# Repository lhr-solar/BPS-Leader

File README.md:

# Battery Protection System Leader
All firmware for the Battery Protection System Leader board.

## Setup
Development is done on a Linux environment to build, flash, and debug firmware

Follow this [guide](https://cloud.wikis.utexas.edu/wiki/spaces/LHRSOLAR/pages/28287146/Setting+up+an+Embedded+Development+Environment) to setup an Embedded Development Environment. We primarily use the Windows Subsystem for Linxu (make sure you are using WSL2 and not WSL1).  
After cloning the repo, enter the Embedded-Sharepoint directory an run `./install.sh` to install all needed dependencies. 

### Cloning the Repo
You must clone this repo using SSH. If you do not have an SSH key with Github setup then follow this [guide](https://docs.github.com/en/github/authenticating-to-github/generating-a-new-ssh-key-and-adding-it-to-the-ssh-agent). Note that you must follow the steps while in WSL.

Once SSH is setup and you can this to clone this repository. We append `` --recursive`` to the end to also clone the Embedded-Sharepoint reposistory. 
```
git clone --recursive
```
If you already cloned the repo but don't have the submodules, enter the following commands:

```
git submodule init
git submodule update --remote
```

## Building
Run `make help` for more information on usage.  
When calling any of the following commands, make sure you are in the top level of the repo.

Call `make` to build the release version of the codebase. By default the BPS builds for the STM32F413RHT microcontroller, but you can change that by changing the ` PROJECT_TARGET` field to be the mcu you'd like to compile for

Call `make clean` if the build fails for any reason other than syntax related.

### How to build a test
To build a new test, you need to use the following command:
`make TEST=x` where x is the name of the test file without the .c suffix.

## Flashing
Call `make flash` to flash the most recently built BPS code.  
If using WSL, you must use use usbipd to connect your port to WSL.

There is also a guide on how to flash with the Nucleos [here](https://cloud.wikis.utexas.edu/wiki/spaces/LHRSOLAR/pages/28286498/Flashing+and+debugging+code+on+an+MCU)

## Rules
Commit frequently into your own branches. Create a Pull Request whenever you are ready to add you working code to the master branch. Make sure that your code compiles without any errors or warnings before you open a pull request. At least one approver must approve your pull request before it can be merged. The reviewers will make sure everything is up to par with the coding standards.

### Code Reviews
You can review a pull request even if you are not an approver. In addition to helping us catch bugs, code reviews are a good opportunity to learn more about the BPS codebase. Some examples on what you can include in a code review are:
- Ask why the author wrote a certain part of code in a way they did
- Point out potential bugs in the code
- Point out that part of the code is not well documented or hard to read

You can either approve, comment, or request changes at the end of your pull request. These are the scenarios in which you would use each option:
- **Approve:** You are signing off that this pull request is ready to merge. You and the pull request author "own" this part of the code now.
- **Request Changes:** You have found problems with the code that must be addressed before it can be merged. Note that this will block the pull request from merging until you re-review the code.
- **Comment:** Do this if you do not want to explicitly approve or request changes.

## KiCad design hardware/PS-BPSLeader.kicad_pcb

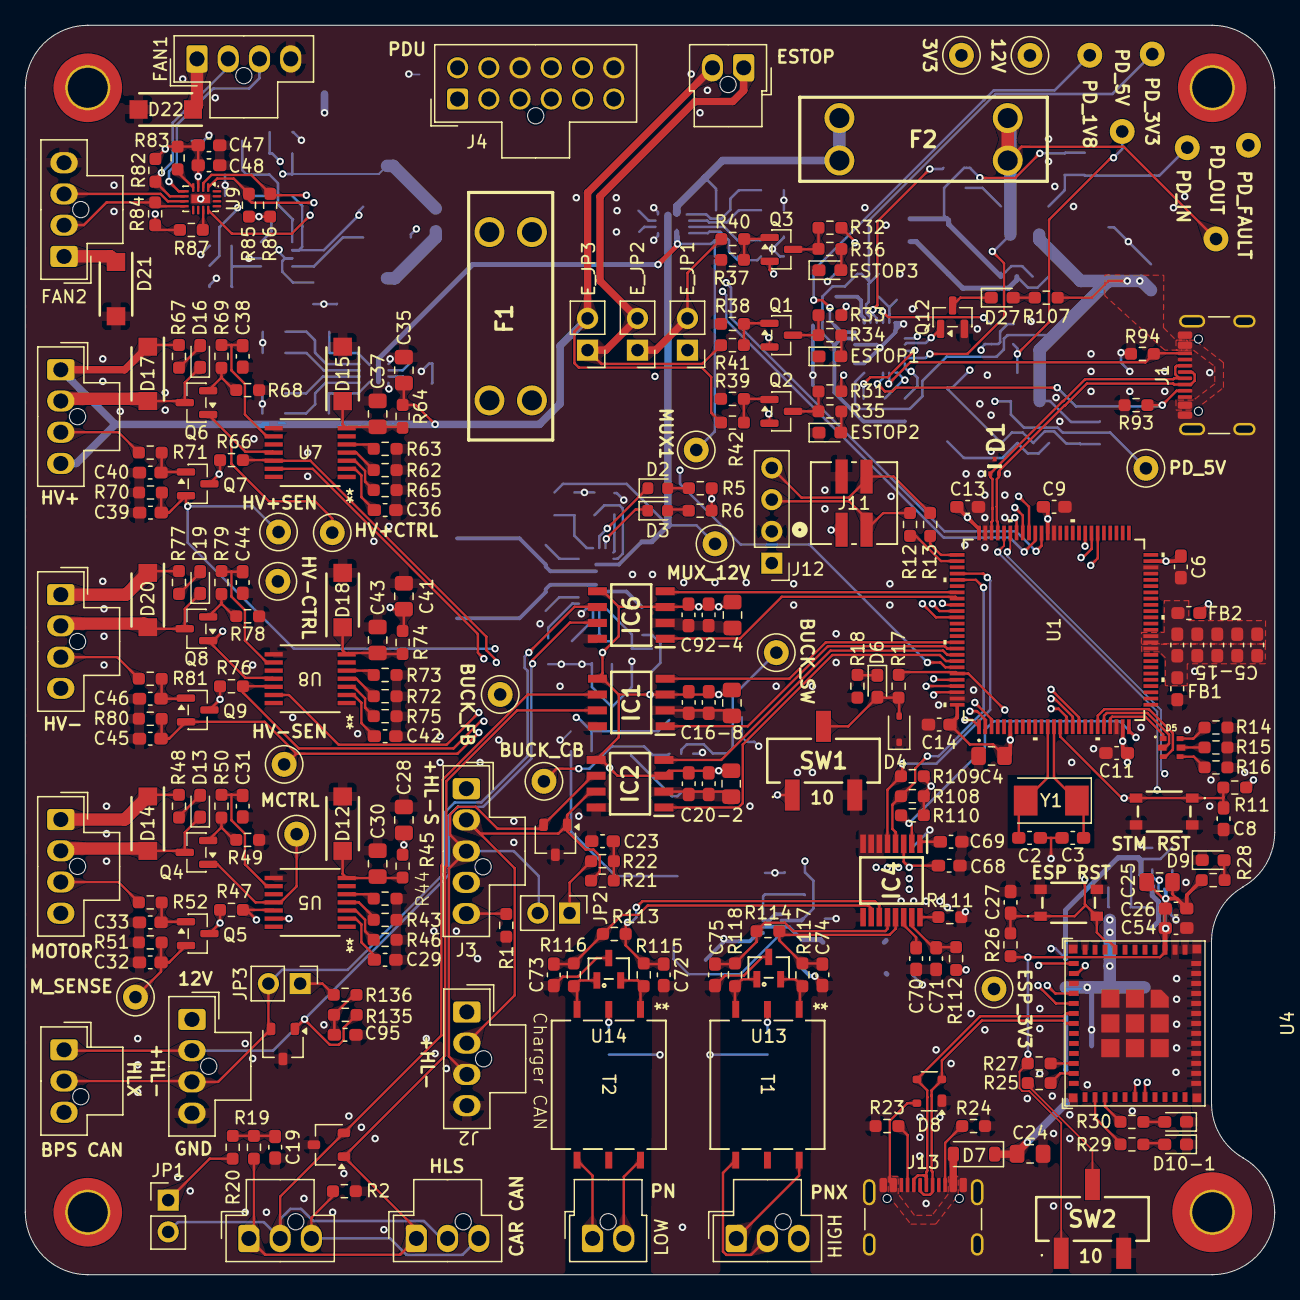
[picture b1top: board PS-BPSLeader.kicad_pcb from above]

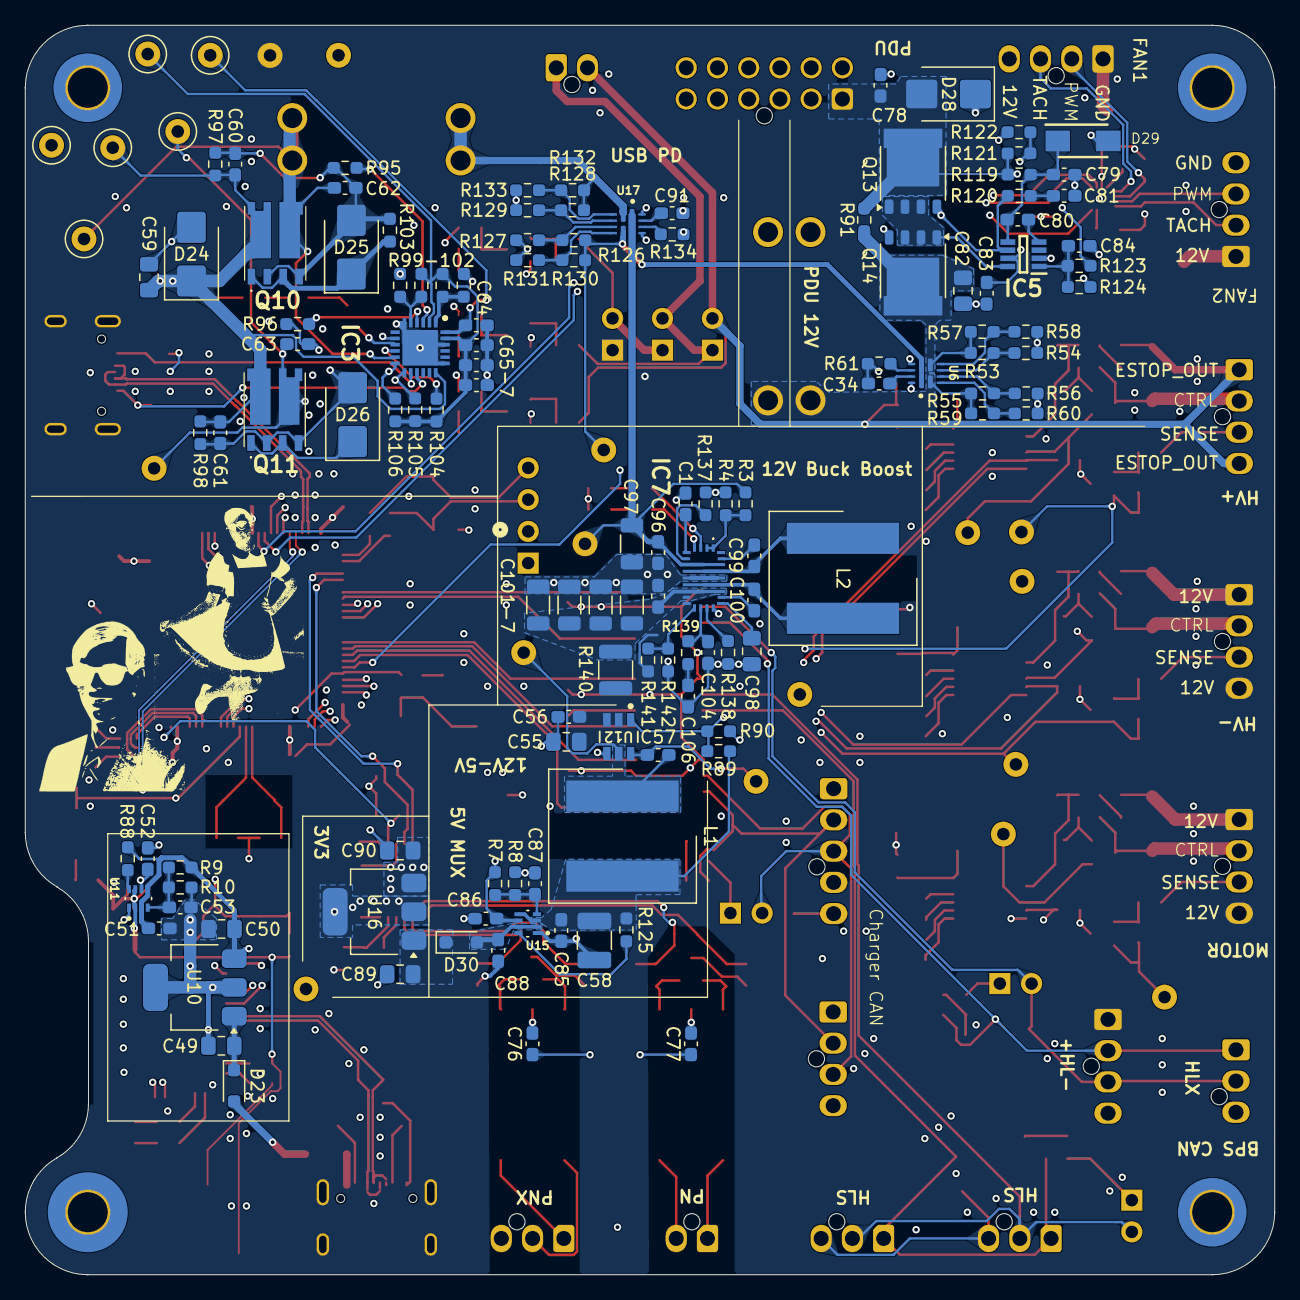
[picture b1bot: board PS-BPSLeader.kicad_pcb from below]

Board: 4 copper layers, 100.0 x 100.0 mm, 385 parts (131 on the bottom side), 230 nets.

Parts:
C1: 7.5n; C_0603_1608Metric_Pad1.08x0.95mm_HandSolder
C2, C3: 26p; C_0603_1608Metric_Pad1.08x0.95mm_HandSolder
C4, C16, C20, C49, C50, C82, C89, C90, C92: 10u; C_0805_2012Metric_Pad1.18x1.45mm_HandSolder
C5, C6, C7, C8, C9, C11, C13, C14, C15, C17, C18, C19, C21, C22, C23, C33, C40, C46, C68, C71, C78, C83, C84, C93, C94, C95, C96, C99, C100, C107: 0.1u; C_0603_1608Metric_Pad1.08x0.95mm_HandSolder
C10, C12, C29, C32, C34, C36, C39, C42, C45, C47, C48, C79, C91: 1u; C_0603_1608Metric_Pad1.08x0.95mm_HandSolder
C24, C25, C59: 10uF; C_0805_2012Metric_Pad1.18x1.45mm_HandSolder
C26, C27, C51, C52, C53, C54, C66, C67, C85, C86, C87, C88: 0.1uF; C_0603_1608Metric_Pad1.08x0.95mm_HandSolder
C28, C30, C35, C37, C41, C43, C55, C98: 4.7u; C_0805_2012Metric_Pad1.18x1.45mm_HandSolder
C31, C38, C44: 0.1n; C_0603_1608Metric_Pad1.08x0.95mm_HandSolder
C56, C57: 100n; C_0603_1608Metric_Pad1.08x0.95mm_HandSolder
C58: 47u; C_1210_3225Metric_Pad1.33x2.70mm_HandSolder
C60, C61, C62, C63, C64, C65: 1uF; C_0603_1608Metric_Pad1.08x0.95mm_HandSolder
C69, C70: 0.22u; C_0603_1608Metric_Pad1.08x0.95mm_HandSolder
C72, C73, C74, C75, C76, C77: 100pF; C_0603_1608Metric_Pad1.08x0.95mm_HandSolder
C80: 220n; C_0603_1608Metric_Pad1.08x0.95mm_HandSolder
C81: 10n; C_0603_1608Metric_Pad1.08x0.95mm_HandSolder
C97, C101, C102, C103, C105: 22u; C_1206_3216Metric
C104: 45p; C_0603_1608Metric_Pad1.08x0.95mm_HandSolder
C106: 90n; C_0603_1608Metric_Pad1.08x0.95mm_HandSolder
D1: TPD2EUSB30DRTR
D2, D3: LED; LED_0603_1608Metric
D4: TVS; D_SOD-323
D5: RGB_LED
D6: LED; LED_0603_1608Metric_Pad1.05x0.95mm_HandSolder
D7: 1N5819HW-7-F; D_SOD-123
D8: SP0503BAHT; SOT-143
D9: ESP_PWR; LED_0603_1608Metric_Pad1.05x0.95mm_HandSolder
D10: ESP_LED1; LED_0603_1608Metric_Pad1.05x0.95mm_HandSolder
D11: ESP_LED2; LED_0603_1608Metric_Pad1.05x0.95mm_HandSolder
D12, D14, D15, D17, D18, D20, D21, D22: VSSAF522-M3/H; SODFL5226X100N
D13, D16, D19: Contact; LED_0603_1608Metric_Pad1.05x0.95mm_HandSolder
D23, D30: SBA130CH-AU_R1_000A1; D_SOD-323_HandSoldering
D24: SMBJ24A-E3_52; D_SMB
D25, D26: SMBJ10A-E3_52; D_SMB
D27: FAULT; LED_0603_1608Metric_Pad1.05x0.95mm_HandSolder
D28: SMBJ15CA; D_SMB
D29: SMAF4758A; SODFL5026X125N
ESTOP1, ESTOP2, ESTOP3: LED; LED_0603_1608Metric_Pad1.05x0.95mm_HandSolder
E_JP1, E_JP2, E_JP3: Jumper_2_Open; PinHeader_1x02_P2.54mm_Vertical
F1, F2: 5A; Fuse-3557-2
FAN1, FAN2: Conn_01x04; Molex_Nano-Fit_105309-xx04_1x04_P2.50mm_Vertical
FB1, FB2: FerriteBead; L_0603_1608Metric_Pad1.05x0.95mm_HandSolder
H1: MountingHole_Pad; MountingHole_3.2mm_M3_Pad_TopBottom
H2, H3, H4: MountingHole_Pad; MountingHole_3.2mm_M3_ISO14580_Pad_TopBottom
IC1, IC2, IC6: TCAN3413DR
IC3: CYPD3177-24LQXQ
IC4: BQ79600PWRQ1; SOP65P640X120-16N
IC5: LM74502DDFR
IC7: TPS552872RYQR; TPS552892QWRYQRQ1
J1, J13: USB_C_Receptacle_USB2.0_16P; USB_C_Receptacle_GCT_USB4105-xx-A_16P_TopMnt_Horizontal
J2: ELCON CAN DEBUG; Molex_Nano-Fit_105309-xx04_1x04_P2.50mm_Vertical
J3: ELCON CAN; Molex_Nano-Fit_105309-xx05_1x05_P2.50mm_Vertical
J4: Conn_02x06_Counter_Clockwise; Molex_Nano-Fit_105310-xx12_2x06_P2.50mm_Vertical
J5: CAR CAN IN; Molex_Nano-Fit_105309-xx03_1x03_P2.50mm_Vertical
J6: CAR CAN OUT; Molex_Nano-Fit_105309-xx03_1x03_P2.50mm_Vertical
J7: BPS CAN DEBUG; Molex_Nano-Fit_105309-xx04_1x04_P2.50mm_Vertical
J8: BPS CAN; Molex_Nano-Fit_105309-xx03_1x03_P2.50mm_Vertical
J9: High Side Conn; Molex_Nano-Fit_105309-xx03_1x03_P2.50mm_Vertical
J10: Low SIde Conn; Molex_Nano-Fit_105309-xx02_1x02_P2.50mm_Vertical
J11: SWD_Header; SWD_Conn
J12: SWD; PinHeader_1x04_P2.54mm_Vertical
J14: Conn_01x02; Molex_Nano-Fit_105309-xx02_1x02_P2.50mm_Vertical
J15, J16, J17: Contactor Connector; Molex_Nano-Fit_105309-xx04_1x04_P2.50mm_Vertical
JP1, JP2, JP3: TRM; PinHeader_1x02_P2.54mm_Vertical
L1: 8.2u; 74439369082
L2: 4.7u; 74439369082
LOGO1: Dr. Hallock; LHRs_LOGO
LOGO2: Dr. Hallock; Hallock_Image_Tiny
Q1, Q2, Q3: SQ2315CES-T1_GE3; SOT-23
Q4, Q5, Q6, Q7, Q8, Q9, Q12: IRLML0030; SOT-23
Q10, Q11: SI7997DP-T1-GE3
Q13, Q14: PSMN012-100YS; LFPAK56
R1, R2, R44, R63, R73, R91: 0; R_0603_1608Metric_Pad0.98x0.95mm_HandSolder
R3: 30.1k; R_0603_1608Metric_Pad0.98x0.95mm_HandSolder
R4, R54, R56, R58, R60, R127, R129, R131, R133: 5k; R_0603_1608Metric_Pad0.98x0.95mm_HandSolder
R5, R6, R14, R15, R16, R18, R28, R29, R30, R34, R35, R36, R45, R50, R64, R69, R74, R79, R95, R96, R101, R113, R114: 1k; R_0603_1608Metric_Pad0.98x0.95mm_HandSolder
R7: 16k; R_0603_1608Metric_Pad0.98x0.95mm_HandSolder
R8, R104: 4.7k; R_0603_1608Metric_Pad0.98x0.95mm_HandSolder
R9: 18k; R_0603_1608Metric_Pad0.98x0.95mm_HandSolder
R10, R11, R17, R25, R26, R27, R31, R32, R33, R37, R38, R39, R47, R51, R52, R66, R70, R71, R76, R80, R81, R82, R84, R85, R86, R88, R97, R107, R108, R109, R119, R125: 10k; R_0603_1608Metric_Pad0.98x0.95mm_HandSolder
R12, R13: 22; R_0603_1608Metric_Pad0.98x0.95mm_HandSolder
R19, R20, R21, R22, R135, R136: 60; R_0603_1608Metric_Pad0.98x0.95mm_HandSolder
R23, R24, R93, R94, R99, R100, R102: 5.1k; R_0603_1608Metric_Pad0.98x0.95mm_HandSolder
R40, R41, R42, R83, R87: 33k; R_0603_1608Metric_Pad0.98x0.95mm_HandSolder
R43, R62, R72: 66.67k; R_0603_1608Metric_Pad0.98x0.95mm_HandSolder
R46, R65, R75: 120k; R_0603_1608Metric_Pad0.98x0.95mm_HandSolder
R48, R67, R77: 4.3k; R_0603_1608Metric_Pad0.98x0.95mm_HandSolder
R49, R68, R78: 1; R_0603_1608Metric_Pad0.98x0.95mm_HandSolder
R53, R126, R132: 57.6k; R_0603_1608Metric_Pad0.98x0.95mm_HandSolder
R55: 67.3k; R_0603_1608Metric_Pad0.98x0.95mm_HandSolder
R57, R130: 26.1k; R_0603_1608Metric_Pad0.98x0.95mm_HandSolder
R59: 37.4k; R_0603_1608Metric_Pad0.98x0.95mm_HandSolder
R61, R134: 22.1k; R_0603_1608Metric_Pad0.98x0.95mm_HandSolder
R89, R110, R111, R121, R123, R128, R141: 100k; R_0603_1608Metric_Pad0.98x0.95mm_HandSolder
R90: 19.1k; R_0603_1608Metric_Pad0.98x0.95mm_HandSolder
R98, R103: 49.9k; R_0603_1608Metric_Pad0.98x0.95mm_HandSolder
R105, R106: 2.2k; R_0603_1608Metric_Pad0.98x0.95mm_HandSolder
R112: 10; R_0603_1608Metric_Pad0.98x0.95mm_HandSolder
R115, R116, R117, R118: 51; R_0603_1608Metric_Pad0.98x0.95mm_HandSolder
R120: 33; R_0603_1608Metric_Pad0.98x0.95mm_HandSolder
R122: 7.32k; R_0603_1608Metric_Pad0.98x0.95mm_HandSolder
R124: 15.8k; R_0603_1608Metric_Pad0.98x0.95mm_HandSolder
R137: 50k; R_0603_1608Metric_Pad0.98x0.95mm_HandSolder
R138: R_US; R_0603_1608Metric_Pad0.98x0.95mm_HandSolder
R139: 1.455k; R_0603_1608Metric_Pad0.98x0.95mm_HandSolder
R140: 12.5m; R_1210_3225Metric
R142: 11.1k; R_0603_1608Metric_Pad0.98x0.95mm_HandSolder
Reset1: Reset; TL3365AF180QG
SW1: SW_SPDT; BootSW
SW2: BOOT Switch; BootSW
SW3: RESET Button; TL3365AF180QG
T1, T2: HMU1228NL; HMU1228NL_PUL
TP1: PD_5V; TestPoint_Loop_D1.80mm_Drill1.0mm_Beaded
TP3: PDU_ELCON; TestPoint_Loop_D1.80mm_Drill1.0mm_Beaded
TP4: MUX_12V; TestPoint_Loop_D1.80mm_Drill1.0mm_Beaded
TP5, TP7, TP9: ctrl; TestPoint_Loop_D1.80mm_Drill1.0mm_Beaded
TP6, TP8, TP10: Sense; TestPoint_Loop_D1.80mm_Drill1.0mm_Beaded
TP11: V_in_12V; TestPoint_Loop_D1.80mm_Drill1.0mm_Beaded
TP12: CB; TestPoint_Loop_D1.80mm_Drill1.0mm_Beaded
TP13: FB; TestPoint_Loop_D1.80mm_Drill1.0mm_Beaded
TP14: SW; TestPoint_Loop_D1.80mm_Drill1.0mm_Beaded
TP15: VBUS_IN; TestPoint_Loop_D1.80mm_Drill1.0mm_Beaded
TP16: PD_VBUS_OUT; TestPoint_Loop_D1.80mm_Drill1.0mm_Beaded
TP17: PD_5V_OUT; TestPoint_Loop_D1.80mm_Drill1.0mm_Beaded
TP18: PD_1V8; TestPoint_Loop_D1.80mm_Drill1.0mm_Beaded
TP19: PD_3V3; TestPoint_Loop_D1.80mm_Drill1.0mm_Beaded
TP20: PD_FAULT; TestPoint_Loop_D1.80mm_Drill1.0mm_Beaded
TP_3.3V1, TP_3.3V2: 3.3V; TestPoint_Loop_D1.80mm_Drill1.0mm_Beaded
U1: STM32G473VETx; 100PinMCU
U2, U3, U18: CDSOT23-T24CAN
U4: ESP32-C6-MINI-1
U5, U7, U8: DRV110APWR; PW14_TEX
U6, U17: TPS2121RUXR
U9: EMC2305-1-AP-TR; QFN-16-1EP_1.8x2.6mm_P0.4mm_EP0.7x1.5mm
U10, U16: MCP1826S; SOT-223-3_TabPin2
U11, U15: TPS2117DRLR
U12: LMR51635XDDCR; DDC0006A-MFG
U13, U14: PESD5V0L2BT; SOT23_NXP
Y1: Crystal; Crystal_SMD_Abracon_ABM3-2Pin_5.0x3.2mm

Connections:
+3.3V: C4.1, C6.1, C9.1, C11.1, C13.1, C14.1, C16.1, C17.1, C18.1, C20.1, C21.1, C22.1, C47.1, C48.1, C52.1, C68.1, C90.2, C92.1, C93.1, C94.1, FB2.1, IC1.3 (VCC), IC1.5 (SHDNV_IO), IC2.3 (VCC), IC2.5 (SHDNV_IO), IC4.3 (VIO), IC6.3 (VCC), IC6.5 (SHDNV_IO), J11.1, J12.1, Q1.2 (S), Q2.2 (S), Q3.2 (S), Q5.3 (D), Q7.3 (D), Q9.3 (D), R5.1, R6.1, R11.2, R47.2, R66.2, R76.2, R82.1, R83.1, R84.1, R85.1, R86.1, R87.1, R108.1, R109.1, R110.1, SW1.1 (A), TP_3.3V2.1 (1_1), U1.6 (VBAT), U1.24 (VDD), U1.49 (VDD), U1.64 (VDD), U1.75 (VDD), U1.100 (VDD), U9.3 (VDD), U11.6 (VIN2), U16.3 (VO)
+3.3V_ESP: C25.1, C25.2, C26.1, C26.2, C54.1, R26.1, R27.2, R28.1, SW2.1 (A), U4.3 (3V3), U11.2 (VOUT), U11.7 (VOUT__1)
+5V: C88.1, D30.2 (A), U15.2 (VOUT), U15.7 (VOUT__1)
+12V: C28.1, C41.1, C55.1, C56.1, D14.1 (K), D20.1 (K), D21.1 (K), D22.1 (K), E_JP1.1 (A), FAN1.1, FAN2.1, IC7.13 (ISN), J7.1 (12V), J15.1 (Con+(12V)), J15.4 (Sense+(12V)), J17.1 (Con+(12V)), J17.4 (Sense+(12V)), R45.2, R48.2, R74.2, R77.2, R112.2, R140.2, R141.2, TP11.1 (1_1), U12.2 (EN), U12.3 (VIN)
/BMS/COMHN: C75.1, IC4.12 (COMHN), R114.2, R118.1
/BMS/COMHP: C74.1, IC4.13 (COMHP), R114.1, R117.1
/BMS/COMLN: C72.1, IC4.11 (COMLN), R113.1, R115.1
/BMS/COMLP: C73.1, IC4.10 (COMLP), R113.2, R116.1
/BMS/INH: IC4.16 (INH), R111.1
/BMS_NFAULT: IC4.2 (NFAULT), R110.2, U1.25 (PA3)
/BMS_UART_RX: IC4.4 (MOSI/RX), R108.2, U1.80 (PC11)
/BMS_UART_TX: IC4.5 (MISO/TX), R109.2, U1.79 (PC10)
/BPS_CAN_H: IC6.7 (CANH), J7.2 (CAN_H), J8.1 (CAN_H), R135.1, U18.1 (CAN_H)
/BPS_CAN_L: IC6.6 (CANL), J7.3 (CAN_L), J8.2 (CAN_L), JP3.2 (B), U18.2 (CAN_L)
/CAR_CAN_H: IC1.7 (CANH), J5.1 (CAN_H), J6.1 (CAN_H), R19.1, U2.1 (CAN_H)
/CAR_CAN_L: IC1.6 (CANL), J5.2 (CAN_L), J6.2 (CAN_L), JP1.2 (B), U2.2 (CAN_L)
/CHARGER_CAN_H: IC2.7 (CANH), J2.2 (CAN_H), J3.2 (CAN_H), R21.1, U3.1 (CAN_H)
/CHARGER_CAN_L: IC2.6 (CANL), J2.3 (CAN_L), J3.3 (CAN_L), JP2.2 (B), U3.2 (CAN_L)
/ELCON_LV+: F1.1, J2.1 (12V), J3.1 (12V)
/ESTOP_1-/2+: E_JP1.2 (B), E_JP2.1 (A), R40.2
/ESTOP_1_SENSE: R32.2, U1.84 (PD2)
/ESTOP_2-: E_JP2.2 (B), E_JP3.1 (A), J14.1, R41.2
/ESTOP_2_SENSE: R33.2, U1.85 (PD3)
/ESTOP_3_SENSE: R31.2, U1.86 (PD4)
/ESTOP_OUT: C35.1, D17.1 (K), E_JP3.2 (B), J14.2, J16.1 (Con+(12V)), J16.4 (Sense+(12V)), R42.2, R64.2, R67.2
/FAN_ALERT: U1.94 (PB7), U9.12 (*ALERT)
/FAN_SCL: R86.2, U1.65 (PC6), U9.2 (SMCLK)
/FAN_SDA: R85.2, U1.66 (PC7), U9.1 (SMDATA)
/Fan/ADDRESS_PULLUP: R83.2, U9.4 (ADDR_SEL)
/Fan/CLK_PULLUP: R87.2, U9.11 (CLK)
/Fan/FAN_1_PWM: FAN1.3, U9.5 (PWM1)
/Fan/FAN_1_TACH: FAN1.2, R82.2, U9.6 (TACH1)
/Fan/FAN_2_PWM: FAN2.3, U9.7 (PWM2)
/Fan/FAN_2_TACH: FAN2.2, R84.2, U9.8 (TACH2)
/HV+ Contactor/Econ_Sense: C38.1, R69.1, U7.9 (SENSE)
/HV+ Contactor/HV_CONTROL: D16.1 (K), D17.2 (A), J16.2 (Con-), Q6.3 (D)
/HV+_CTRL: U1.98 (PE1), U7.13 (EN)
/HV+_ECON: R66.1, U1.97 (PE0), U7.12 (STATUS)
/HV+_SENSE: C39.2, Q7.2 (S), R70.2, TP8.1 (1_1), U1.96 (PB9)
/HV- Contactor/Econ_Sense: C44.1, R79.1, U8.9 (SENSE)
/HV- Contactor/HV_CONTROL: D19.1 (K), D20.2 (A), J17.2 (Con-), Q8.3 (D)
/HV-_CTRL: U1.3 (PE4), U8.13 (EN)
/HV-_ECON: R76.1, U1.2 (PE3), U8.12 (STATUS)
/HV-_SENSE: C45.2, Q9.2 (S), R80.2, TP10.1 (1_1), U1.1 (PE2)
/MOTOR_CTRL: U1.17 (PC2), U5.13 (EN)
/MOTOR_ECON: R47.1, U1.16 (PC1), U5.12 (STATUS)
/MOTOR_SENSE: C32.2, Q5.2 (S), R51.2, TP6.1 (1_1), U1.15 (PC0)
/Motor_Contactor/Econ_Sense: C31.1, R50.1, U5.9 (SENSE)
/Motor_Contactor/HV_CONTROL: D13.1 (K), D14.2 (A), J15.2 (Con-), Q4.3 (D)
/PDU_LV+: C78.1, D28.2 (A2), J4.1, Q13.5, R91.1, R119.2, R121.1, R123.1
/Peripherals/100PinMCU/GNDA: C5.2, C7.2, C10.2, C12.2, C15.2, FB1.1, U1.35 (VSSA)
/Peripherals/100PinMCU/PA0: D5.5, U1.20 (PA0-GPIO_BLUE)
/Peripherals/100PinMCU/PA1: D5.3, U1.21 (PA1-GPIO_RED)
/Peripherals/100PinMCU/PA2: D5.1, U1.22 (PA2-GPIO_GREEN)
/Peripherals/100PinMCU/SWCLK: R12.1, U1.77 (PA14)
/Peripherals/100PinMCU/SWDIO: R13.1, U1.76 (PA13)
/Peripherals/100PinMCU/VDDA: C5.1, C7.1, C10.1, C12.1, C15.1, FB2.2, U1.36 (VREF+), U1.37 (VDDA)
/Peripherals/BPS_CAN_RX: IC6.4 (RXD), U1.82 (PD0)
/Peripherals/BPS_CAN_TX: IC6.1 (TXD), U1.83 (PD1)
/Peripherals/CAR_CAN_RX: IC1.4 (RXD), U1.90 (PB3)
/Peripherals/CAR_CAN_TX: IC1.1 (TXD), U1.91 (PB4)
/Peripherals/CHARGER_CAN_RX: IC2.4 (RXD), U1.92 (PB5)
/Peripherals/CHARGER_CAN_TX: IC2.1 (TXD), U1.93 (PB6)
/Peripherals/ESP32/+5V_LDO_IN: C24.1, D7.1 (K), D23.2 (A)
/Peripherals/ESP32/BOOT: R25.1, U4.23 (GPIO9)
/Peripherals/ESP32/LED1: R29.1, U4.26 (GPIO20)
/Peripherals/ESP32/LED2: R30.1, U4.27 (GPIO21)
/Peripherals/ESP32/USB_D+: D8.2 (K), J13.A6 (D+), J13.B6 (D+), U4.18 (GPIO13/USB_D+)
/Peripherals/ESP32/USB_D-: D8.3 (K), J13.A7 (D-), J13.B7 (D-), U4.17 (GPIO12/USB_D-)
/Peripherals/ESP32/VBUSB: D7.2 (A), D8.4 (K), J13.A4 (VBUS), J13.A9 (VBUS), J13.B4 (VBUS), J13.B9 (VBUS)
/Peripherals/ESP32_LDO/Vout: C50.2, C51.1, R9.1, R88.1, TP_3.3V1.1 (1_1), U10.3 (VO), U11.3 (VIN1), U11.5 (MODE)
/Peripherals/ESP32_Power_Mux/PR1: C53.1, R9.2, R10.1, U11.4 (PR1)
/Peripherals/ESP_GPIO3: U1.56 (PD9), U4.15 (MTCK/GPIO6/ADC1_CH6)
/Peripherals/ESP_GPIO4: U1.57 (PD10), U4.16 (MTDO/GPIO7)
/Peripherals/ESP_NRST: C27.1, R26.2, SW3.1, U1.58 (PD11), U4.8 (EN/CHIP_PU)
/Peripherals/STM_BOOT: R17.1, U1.95 (PB8-BOOT0), U4.12 (GPIO0/ADC1_CH0/XTAL_32K_P)
/Peripherals/STM_NRST: C8.1, R11.1, Reset1.1, U1.14 (PG10-NRST), U4.13 (GPIO1/ADC1_CH1/XTAL_32K_N)
/Peripherals/STM_RX: U1.71 (PA10), U4.31 (U0TXD/GPIO16)
/Peripherals/STM_TX: U1.70 (PA9), U4.30 (U0RXD/GPIO17)
/Power/5V_BUCK: C58.1, C85.1, L1.2, R89.1, R125.1, U15.3 (VIN1), U15.5 (MODE)
/Power/12VBuck/CB: C57.1, TP12.1 (1_1), U12.6 (CB)
/Power/12VBuck/FB: R89.2, R90.1, TP13.1 (1_1), U12.1 (FB)
/Power/12VBuck/SW: C57.2, L1.1, TP14.1 (1_1), U12.5 (SW)
/Power/12V_CC: D3.1 (K), IC7.4 (~CC)
/Power/12V_DITH: C1.1, IC7.5 (DITH/SYNC)
/Power/12V_PG: D2.1 (K), IC7.3 (PG)
/Power/EN: IC7.1 (EN/UVLO), IC7.2 (MODE), R3.2, R4.1
/Power/MUX_12V: C96.1, C97.1, IC7.7 (VIN), R3.1, TP4.1 (1_1), U17.1 (OUT), U17.8 (OUT)
/Power/PDU_12V: C82.1, Q14.5, R53.1, R57.1, R91.2, U6.7 (IN1)
/Power/PD_5V_OUT: C63.1, C86.1, Q11.5 (D2), Q11.6 (D2), Q11.10 (D2), Q11.12 (D2), R7.1, TP1.1 (1_1), TP17.1 (1_1), U15.6 (VIN2)
/Power/PowerProtection/EN/UVLO: C84.2, IC5.1 (EN/UVLO), R123.2, R124.2
/Power/PowerProtection/OV: C83.2, IC5.7 (OV), R121.2, R122.1
/Power/PowerProtection/gate: IC5.6 (GATE), Q13.4, Q14.4, R120.2
/Power/PowerProtection/source: IC5.8 (SRC), Q13.1, Q13.2, Q13.3, Q14.1, Q14.2, Q14.3
/Power/Power_5VMux/PR1: C87.1, R7.2, R8.1, U15.4 (PR1)
/Power/Power_Mux_PD/CP2: R132.2, R133.1, U17.3 (CP2)
/Power/Power_Mux_PD/OV1: R126.2, R127.1, U17.5 (OV1)
/Power/Power_Mux_PD/OV2: R128.2, R129.1, U17.4 (OV2)
/Power/Power_Mux_PD/PRI: R130.2, R131.1, U17.6 (PR1)
/Power/Power_Mux_PD/Vin1: R126.1, R130.1, TP3.1 (1_1), U6.1 (OUT), U6.8 (OUT), U17.7 (IN1)
/Power/Power_Mux_PD/Vin2: F2.2, R128.1, R132.1, U17.2 (IN2)
/Power/Power_Mux_PDU_ELCON/CP2: R59.2, R60.1, U6.3 (CP2)
/Power/Power_Mux_PDU_ELCON/OV1: R53.2, R54.1, U6.5 (OV1)
/Power/Power_Mux_PDU_ELCON/OV2: R55.2, R56.1, U6.4 (OV2)
/Power/Power_Mux_PDU_ELCON/PRI: R57.2, R58.1, U6.6 (PR1)
/Power/Power_Mux_PDU_ELCON/Vin2: F1.2, R55.1, R59.1, U6.2 (IN2)
/Power/Power_USB_PD/ISINK_COARSE: IC3.5 (ISNK_COARSE), R100.2, R102.1
/Power/Power_USB_PD/PD_1V8: C64.2, IC3.24 (VCCD), TP18.1 (1_1)
/Power/Power_USB_PD/PD_3V3: C65.1, C66.1, C67.1, IC3.2 (VBUS_MAX), IC3.23 (VDDD), R99.1, R100.1, R104.1, R105.1, R106.1, TP19.1 (1_1)
/Power/Power_USB_PD/PD_FAULT: IC3.9 (FAULT), Q12.1 (G), TP20.1 (1_1)
/Power/Power_USB_PD/SAFE_PWR_EN: IC3.4 (SAFE_PWR_EN), R96.2
/Power/Power_USB_PD/VBUS_FET_EN: IC3.3 (VBUS_FET_EN), R95.2
/Power/Power_USB_PD/VBUS_MIN: IC3.1 (VBUS_MIN), R99.2, R101.1
/Power/USB_PD_OUT: C62.1, F2.1, IC3.11 (VDC_OUT), Q10.5 (D2), Q10.6 (D2), Q10.10 (D2), Q10.12 (D2), TP16.1 (1_1)
/SHIELD: J5.3 (SHIELD), J6.3 (SHIELD), R2.1
/USB_CC1: IC3.15 (CC1), J1.A5 (CC1), R93.1
/USB_CC2: IC3.14 (CC2), J1.B5 (CC2), R94.1
/USB_D+: D1.1 (D+), J1.A6 (D+), J1.B6 (D+), U1.73 (PA12)
/USB_D-: D1.2 (D-), J1.A7 (D-), J1.B7 (D-), U1.72 (PA11)
/USB_GPIO: IC3.8 (GPIO_1), U1.69 (PA8)
/USB_SCL: IC3.13 (HPI_SCL), R105.2, U1.67 (PC8)
/USB_SDA: IC3.12 (HPI_SDA), R106.2, U1.68 (PC9)
/USB_VBUS_IN: C59.1, C60.1, C61.1, D24.1 (K), IC3.18 (VBUS_IN), J1.A4 (VBUS), J1.A9 (VBUS), J1.B4 (VBUS), J1.B9 (VBUS), Q10.7 (D1), Q10.8 (D1), Q10.9 (D1), Q10.11 (D1), Q11.7 (D1), Q11.8 (D1), Q11.9 (D1), Q11.11 (D1), R97.2, R98.2, R107.1, TP15.1 (1_1)
/isolatedCOMHN: J9.2, T1.4 (TX-)
/isolatedCOMHP: J9.1, T1.6 (TX+)
/isolatedCOMLN: J10.2, T2.6 (TX+)
/isolatedCOMLP: J10.1, T2.4 (TX-)
GND: C1.2, C2.1, C3.1, C4.2, C6.2, C8.2, C9.2, C11.2, C13.2, C14.2, C16.2, C17.2, C18.2, C19.2, C20.2, C21.2, C22.2, C23.2, C24.2, C27.2, C28.2, C29.2, C30.2, C31.2, C32.1, C33.1, C34.2, C35.2, C36.2, C37.2, C38.2, C39.1, C40.1, C41.2, C42.2, C43.2, C44.2, C45.1, C46.1, C47.2, C48.2, C49.1, C50.1, C51.2, C52.2, C53.2, C54.2, C55.2, C56.2, C58.2, C59.2, C64.1, C65.2, C66.2, C67.2, C68.2, C69.2, C70.2, C71.2, C72.2, C73.2, C74.2, C75.2, C76.1, C77.1, C78.2, C79.1, C81.2, C82.2, C83.1, C84.1, C85.2, C86.2, C87.2, C88.2, C89.1, C90.1, C91.2, C92.2, C93.2, C94.2, C95.2, C96.2, C97.2, C98.2, C101.2, C102.2, C103.2, C104.2, C105.2, C106.2, C107.2, D1.3 (GND), D4.1 (A1), D8.1 (A), D9.1 (K), D10.1 (K), D11.1 (K), D12.2 (A), D15.2 (A), D18.2 (A), D21.2 (A), D22.2 (A), D24.2 (A), D28.1 (A1), D29.2 (A), ESTOP1.1 (K), ESTOP2.1 (K), ESTOP3.1 (K), FAN1.4, FAN2.4, FB1.2, IC1.2 (GND), IC1.8 (STB), IC2.2 (GND), IC2.8 (STB), IC3.6 (ISNK_FINE), IC3.19 (GND_1), IC3.22 (GND_2), IC3.25 (GND_3), IC4.6 (SCLK), IC4.7 (NCS), IC4.8 (NUART/SPI_(SPI_RDY)), IC4.9 (GND), IC5.2 (GND), IC6.2 (GND), IC6.8 (STB), IC7.9 (PGND_1), IC7.17 (AGND), IC7.22 (PGND_2), IC7.23 (PGND_3), J1.A1 (GND), J1.A12 (GND), J1.B1 (GND), J1.B12 (GND), J1.S1 (SHIELD), J1.S2 (Shield), J1.S3 (Shield), J1.S4 (Shield), J2.4 (GND), J3.4 (GND), J4.9, J4.12, J7.4 (GND), J11.2, J12.2, J13.A1 (GND), J13.A12 (GND), J13.B1 (GND), J13.B12 (GND), J13.S1 (SHIELD), J13.S2 (Shield), J13.S3 (Shield), J13.S4 (Shield), Q12.2 (S), R1.2, R2.2, R4.2, R8.2, R10.2, R14.2, R15.2, R16.2, R18.2, R23.2, R24.2, R37.1, R38.1, R39.1, R43.1, R44.1, R46.1, R49.1, R51.1, R54.2, R56.2, R58.2, R60.2, R61.2, R62.1, R63.1, R65.1, R68.1, R70.1, R72.1, R73.1, R75.1, R78.1, R80.1, R90.2, R93.2, R94.2, R101.2, R102.2, R111.2, R122.2, R124.1, R127.2, R129.2, R131.2, R133.2, R134.2, R137.1, R138.1, R142.2, Reset1.2, SW1.3 (C), SW2.3 (C), SW3.2, U1.23 (VSS), U1.48 (VSS), U1.63 (VSS), U1.74 (VSS), U1.99 (VSS), U2.3 (GND), U3.3 (GND), U4.1 (GND), U4.2 (GND), U4.11 (GND), U4.14 (GND), U4.36 (GND), U4.37 (GND), U4.38 (GND), U4.39 (GND), U4.40 (GND), U4.41 (GND), U4.42 (GND), U4.43 (GND), U4.44 (GND), U4.45 (GND), U4.46 (GND), U4.47 (GND), U4.48 (GND), U4.49 (GND), U4.50 (GND), U4.51 (GND), U4.52 (GND), U4.53 (GND), U5.8 (GND), U6.9 (ST), U6.12 (GND), U7.8 (GND), U8.8 (GND), U9.17 (EPAD), U10.2 (GND), U11.1 (GND), U12.4 (GND), U13.3, U14.3, U15.1 (GND), U16.2 (GND), U17.9 (ST), U17.12 (GND), U18.3 (GND)
unnamed: C19.1, R19.2, R20.1
unnamed: C23.1, R21.2, R22.1
unnamed: C81.1, R120.1
unnamed: C95.1, R135.2, R136.1
unnamed: C106.1, R139.2
unnamed: D2.2 (A), R5.2
unnamed: D3.2 (A), R6.2
unnamed: D4.2 (A2), D6.2 (A), R17.2, SW1.2 (B)
unnamed: D5.2, R14.1
unnamed: D5.4, R15.1
unnamed: D5.6, R16.1
unnamed: D6.1 (K), R18.1
unnamed: D9.2 (A), R28.2
unnamed: D10.2 (A), R29.2
unnamed: D11.2 (A), R30.2
unnamed: C30.1, D12.1 (K), R45.1, U5.7 (VIN)
unnamed: D13.2 (A), R48.1
unnamed: C37.1, D15.1 (K), R64.1, U7.7 (VIN)
unnamed: D16.2 (A), R67.1
unnamed: C43.1, D18.1 (K), R74.1, U8.7 (VIN)
unnamed: D19.2 (A), R77.1
unnamed: C49.2, D23.1 (K), U10.1 (VI)
unnamed: C60.2, C62.2, D25.2 (A), Q10.2 (G1), Q10.4 (G2), R95.1, R97.1, R103.1
unnamed: D25.1 (K), Q10.1 (S1), Q10.3 (S2), R103.2
unnamed: C61.2, C63.2, D26.2 (A), Q11.2 (G1), Q11.4 (G2), R96.1, R98.1
unnamed: D26.1 (K), Q11.1 (S1), Q11.3 (S2)
unnamed: D27.2 (A), R107.2
unnamed: D27.1 (K), Q12.3 (D)
unnamed: C79.2, C80.1, D29.1 (K), IC5.5 (VS), R119.1
unnamed: C89.2, D30.1 (K), U16.1 (VI)
unnamed: ESTOP1.2 (A), R34.2
unnamed: ESTOP2.2 (A), R35.2
unnamed: ESTOP3.2 (A), R36.2
unnamed: IC3.10 (FLIP), R104.2
unnamed: C71.1, IC4.15 (BAT), R112.1
unnamed: C70.1, IC4.14 (CVDD)
unnamed: C69.1, IC4.1 (DVDD)
unnamed: C80.2, IC5.4 (VCAP)
unnamed: C99.1, IC7.20 (BOOT1)
unnamed: C100.2, IC7.19 (BOOT2)
unnamed: IC7.16 (CDC), R138.2
unnamed: C104.1, IC7.15 (COMP), R139.1
unnamed: IC7.14 (FB), R141.1, R142.1
unnamed: IC7.6 (FSW), R137.2
unnamed: C101.1, C102.1, C103.1, C105.1, C107.1, IC7.11 (VOUT), IC7.12 (ISP), R140.1
unnamed: C99.2, IC7.8 (SW1), L2.1
unnamed: C100.1, IC7.10 (SW2), L2.2
unnamed: C98.1, IC7.18 (VCC)
unnamed: J3.5 (SHIELD), R1.1
unnamed: J11.3, J12.3, R12.2
unnamed: J11.4, J12.4, R13.2
unnamed: J13.A5 (CC1), R23.1
unnamed: J13.B5 (CC2), R24.1
unnamed: J15.3 (Sense-), R52.1
unnamed: J16.3 (Sense-), R71.1
unnamed: J17.3 (Sense-), R81.1
unnamed: JP1.1 (A), R20.2
unnamed: JP2.1 (A), R22.2
unnamed: JP3.1 (A), R136.2
unnamed: Q1.3 (D), R33.1, R34.1
unnamed: Q1.1 (G), R38.2, R41.1
unnamed: Q2.3 (D), R31.1, R35.1
unnamed: Q2.1 (G), R39.2, R42.1
unnamed: Q3.3 (D), R32.1, R36.1
unnamed: Q3.1 (G), R37.2, R40.1
unnamed: Q4.1 (G), TP5.1 (1_1), U5.11 (OUT)
unnamed: Q4.2 (S), R49.2, R50.2
unnamed: C33.2, Q5.1 (G), R52.2
unnamed: Q6.1 (G), TP7.1 (1_1), U7.11 (OUT)
unnamed: Q6.2 (S), R68.2, R69.2
unnamed: C40.2, Q7.1 (G), R71.2
unnamed: Q8.1 (G), TP9.1 (1_1), U8.11 (OUT)
unnamed: Q8.2 (S), R78.2, R79.2
unnamed: C46.2, Q9.1 (G), R81.2
unnamed: R25.2, SW2.2 (B)
unnamed: C76.2, T1.2 (TCT)
unnamed: R117.2, T1.1 (TD+), U13.2
unnamed: R118.2, T1.3 (TD-), U13.1
unnamed: C77.2, T2.2 (TCT)
unnamed: R115.2, T2.1 (TD+), U14.2
unnamed: R116.2, T2.3 (TD-), U14.1
unnamed: C2.2, U1.12 (PF0-OSC_IN), Y1.2
unnamed: C3.2, U1.13 (PF1-OSC_OUT), Y1.1
unnamed: R27.1, U4.22 (GPIO8)
unnamed: R43.2, U5.4 (HOLD)
unnamed: C29.1, U5.2 (KEEP)
unnamed: R44.2, U5.5 (OSC)
unnamed: R46.2, U5.3 (PEAK)
unnamed: R61.1, U6.10 (ILIM)
unnamed: C34.1, U6.11 (SS)
unnamed: R62.2, U7.4 (HOLD)
unnamed: C36.1, U7.2 (KEEP)
unnamed: R63.2, U7.5 (OSC)
unnamed: R65.2, U7.3 (PEAK)
unnamed: R72.2, U8.4 (HOLD)
unnamed: C42.1, U8.2 (KEEP)
unnamed: R73.2, U8.5 (OSC)
unnamed: R75.2, U8.3 (PEAK)
unnamed: R88.2, U11.8 (ST)
unnamed: R125.2, U15.8 (ST)
unnamed: R134.1, U17.10 (ILIM)
unnamed: C91.1, U17.11 (SS)

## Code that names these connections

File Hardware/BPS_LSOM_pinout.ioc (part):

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Mcu.Name=STM32G473R(B-C-E)Tx
Mcu.Package=LQFP64
Mcu.UserName=STM32G473RETx
PA0.Signal=GPIO_Output
PA1.Signal=GPIO_Output
PA10.Signal=GPIO_Input
PA11.Mode=FDCAN_Activate
PA11.Signal=FDCAN1_RX
PA12.Mode=FDCAN_Activate
PA12.Signal=FDCAN1_TX
PA13.Mode=Serial_Wire
PA13.Signal=SYS_JTMS-SWDIO
PA14.Mode=Serial_Wire
PA14.Signal=SYS_JTCK-SWCLK
PA15.Mode=FDCAN_Activate
PA15.Signal=FDCAN3_TX
PA2.Signal=GPIO_Input
PA3.Signal=GPIO_Input
PA4.Mode=NSS_Signal_Hard_Output
PA4.Signal=SPI1_NSS
PA5.Mode=Full_Duplex_Master
PA5.Signal=SPI1_SCK
PA6.Mode=Full_Duplex_Master
PA6.Signal=SPI1_MISO
PA7.Mode=Full_Duplex_Master
PA7.Signal=SPI1_MOSI
PA8.Mode=FDCAN_Activate
PA8.Signal=FDCAN3_RX
PA9.Mode=IN2-Single-Ended
PA9.Signal=ADC5_IN2
PB0.Signal=GPIO_Input
PB10.Mode=Asynchronous
PB10.Signal=USART3_TX
PB11.Mode=Asynchronous
PB11.Signal=USART3_RX
PB12.Mode=IN11-Single-Ended
PB12.Signal=ADC1_IN11
PB2.Mode=IN12-Single-Ended
PB2.Signal=ADC2_IN12
PB3.Signal=GPIO_Input
PB4.Signal=GPIO_Input
PB5.Signal=GPIO_Input
PB6.Signal=GPIO_Output
PB7.Signal=GPIO_Input
PB8-BOOT0.Signal=GPIO_Input
PC0.Signal=GPIO_Input
PC1.Signal=GPIO_Output
PC10.Mode=Asynchronous
PC10.Signal=UART4_TX
PC11.Mode=Asynchronous
PC11.Signal=UART4_RX
PC12.Signal=GPIO_Output
PC2.Signal=GPIO_Output
PC3.Mode=IN9-Single-Ended
PC3.Signal=ADC1_IN9
PC6.Mode=I2C
PC6.Signal=I2C4_SCL
PC7.Mode=I2C
PC7.Signal=I2C4_SDA
PC8.Mode=I2C
PC8.Signal=I2C3_SCL
PC9.Mode=I2C
PC9.Signal=I2C3_SDA
PD2.Signal=GPIO_Output
PF0-OSC_IN.Mode=HSE-External-Oscillator
PF0-OSC_IN.Signal=RCC_OSC_IN
PF1-OSC_OUT.Mode=HSE-External-Oscillator
PF1-OSC_OUT.Signal=RCC_OSC_OUT
PG10-NRST.Signal=GPIO_Input
RCC.HSE_VALUE=8000000
RCC.SYSCLKFreq_VALUE=16000000
board=custom

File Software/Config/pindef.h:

/* File holds all pin, port, and channel definitions*/

/**
 * @brief object that holds pin num and port of a GPIO pin
 */
typedef struct {
    GPIO_TypeDef* port; // e.g., GPIOA
    uint16_t      pin;  // e.g., GPIO_PIN_3
} GpioPin_t;



// Strobe Connection (+3.3V)
#define STROBE_PIN  GPIO_PIN_2
#define STROBE_PORT GPIOD


// Indication Connection 
#define INDICATION_PIN  GPIO_PIN_12
#define INDICATION_PORT GPIOC

// Heartbeat LED
#define HEARTBEAT_LED_PIN  GPIO_PIN_3
#define HEARTBEAT_LED_PORT GPIOC


// Fan Cip
//------------------------------------------
#define FAN_SCL_PIN GPIO_PIN_8 
#define FAN_SCL_PORT GPIOC

#define FAN_SDA_PIN GPIO_PIN_9
#define FAN_SDA_PORT GPIOC

#define FAN_ALERT_PIN GPIO_PIN_0
#define FAN_ALERT_PORT GPIOC

#define FAN_I2C_CHANNEL I2C3
//------------------------------------------


// SHT4x
//------------------------------------------
#define SHT4x_SCL_PIN GPIO_PIN_6 
#define SHT4x_SCL_PORT GPIOC

#define SHT4x_SDA_PIN GPIO_PIN_7
#define SHT4x_SDA_PORT GPIOC

#define SHT4x_I2C_CHANNEL I2C4
//------------------------------------------


// ESP32
//------------------------------------------
#define ESP_RESET_PIN GPIO_PIN_1 
#define ESP_RESET_PORT GPIOB

#define ESP_UART_CHANNEL LPUART1
//------------------------------------------


// Status LED Shift-Reg PINDEF
//------------------------------------------
#define LED_SER_PIN GPIO_PIN_13  
#define LED_SER_PORT GPIOB

#define LED_RCLK_PIN GPIO_PIN_15 
#define LED_RCLK_PORT GPIOB

#define LED_SRCLK_PIN GPIO_PIN_14
#define LED_SRCLK_PORT GPIOB
//------------------------------------------


// ADC Precharge V
//------------------------------------------
#define ARRAY_V_PIN ADC_NUM_11
#define ARRAY_V_CHANNEL ADC1


#define BATT_V_PIN ADC_NUM_12
#define BATT_V_PORT ADC2
//------------------------------------------


// Car and BPS CAN 
//------------------------------------------
#define BPS_CAN_CHANNEL FDCAN1

#define CAR_CAN_CHANNEL FDCAN3
//------------------------------------------


// HV+ Contactor
//------------------------------------------
#define HV_PLUS_CONTROL_PIN GPIO_PIN_2
#define HV_PLUS_CONTROL_PORT GPIOC

#define HV_PLUS_SENSE_PIN GPIO_PIN_2
#define HV_PLUS_SENSE_PORT GPIOA
//------------------------------------------


// HV- Contactor
//------------------------------------------
#define HV_MINUS_CONTROL_PIN GPIO_PIN_0
#define HV_MINUS_CONTROL_PORT GPIOB

#define HV_MINUS_SENSE_PIN GPIO_PIN_1
#define HV_MINUS_SENSE_PORT GPIOA
//------------------------------------------


// Array Contactor
//------------------------------------------
#define ARRAY_CONTROL_PIN GPIO_PIN_1
#define ARRAY_CONTROL_PORT GPIOC

#define ARRAY_SENSE_PIN GPIO_PIN_0
#define ARRAY_SENSE_PORT GPIOA
//------------------------------------------


// Array Precharge Contactor
//------------------------------------------
#define ARRAY_PRE_CONTROL_PIN GPIO_PIN_9
#define ARRAY_PRE_CONTROL_PORT GPIOB            

#define ARRAY_PRE_SENSE_PIN GPIO_PIN_3
#define ARRAY_PRE_SENSE_PORT GPIOB
//------------------------------------------


// ESTOPs
//------------------------------------------
#define ESTOP1_PIN GPIO_PIN_5
#define ESTOP1_PORT GPIOB

#define ESTOP2_PIN GPIO_PIN_10
#define ESTOP2_PORT GPIOA

#define ESTOP3_PIN GPIO_PIN_4
#define ESTOP3_PORT GPIOB
//------------------------------------------

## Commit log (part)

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2024-04-13 fixed gitignore
2024-04-16 still no compile :(
2024-04-17 added a main (still no compile)
2024-04-17 leader compiles
2024-10-05 initial commit: empty makefile
2024-10-12 embedded-sharepoint compiles with make
2024-10-12 actually compiles embedded sharepoint now
2024-10-12 improved makefile
2024-10-12 better clean
2024-10-19 builds? production code
2024-10-26 builds with test file, error with main
2024-10-26 builds both main & test (but it's hardcoded)
2024-10-26 everything seems to compile properly (compiling for test now excludes main.c)
2024-10-26 improved "make help"; everything compiles
2024-10-26 test folder
2024-10-26 initial makefile review (#1)
    * initial commit: empty makefile
    * embedded-sharepoint compiles with make
    * actually compiles embedded sharepoint now
    * improved makefile
    * added clean in Makefile
    * better clean
2024-11-02 first IDWG draft
2024-11-02 modified makefile to allow passed-in stm targets
2024-11-06 started adding structure
2024-11-06 started messing with Readme
2024-11-06 wahooo
2024-11-06 addded config
2024-11-09 restructure
2024-11-09 fixed flash for my makefile
2024-11-09 fixed ghot spaces in default project target
2024-11-10 still messing with stuff
2024-11-10 dumbass
2024-11-10 fixed some stuff
2024-11-10 who needs to test code
2024-11-13 started testing tasks
2024-11-13 the OS is not OSing
2024-11-15 init task doesn't brick itself
2024-11-16 confirmed flash to nucleo, IWDG continuosly resets though
2024-11-16 IWDG refreshes in time, but with funky timeout
2024-11-16 documented some issues
2024-11-16 IWDG seems to work
2024-12-07 end of workday 12/7/24
2024-12-07 changed c_cpp properties
2024-12-14 20ms timeout, but HAL_Delay(17) trips IWDG
2025-01-11 Updated makefile
2025-01-11 upated safe directory
2025-01-11 pls wokr :sob:
2025-01-11 removed lame comment
2025-01-11 update Embedded-Sharepoint
2025-01-12 removed not needed git safes in devcontainer
2025-01-12 ok maybe i did need it
2025-01-12 let's see if i rlly need it
2025-01-12 lmao i forgot bear
2025-01-15 task stuff is in the works
2025-01-16 task compiles
2025-01-18 added dummy task
2025-01-18 dummy task
2025-01-18 petWatchdog and dummy task run concurrently
2025-01-18 moved stack array
2025-01-18 womp
2025-01-18 wrong branch, deleted comment
2025-01-18 real first commit
2025-01-18 added task schduler stuff (doesn't work) (yet)
2025-01-18 test calls watchdog and dummy task, work hooray
2025-01-18 started semaphore stuff (but i may not know what i'm doing)
2025-01-22 git ignore update
2025-01-22 gpio init moved to IWDG_Init function
2025-01-25 updated IWDG_init to accept function pointer to an error handler
2025-01-25 compiles now lmao
2025-01-25 make sure works on hw
2025-01-25 add temperature task
2025-01-25 add leds to test runtime of diff tasks
2025-01-25 cleaned up some code
2025-01-25 use sharepoint start script
2025-01-25 deleted structure files
2025-01-25 addressed some PR comments, still working on IWDG tests
2025-01-26 fix heartbeat write
2025-01-26 fun compile time messages
2025-01-26 add .DS_Store to gitignore
2025-01-28 add macro concatenation
2025-01-29 updated devcontainer
2025-01-29 update embeddded-sharepoint
2025-01-29 bear debugging
2025-02-05 remove pragma messages
2025-02-05 started this shit again
2025-02-05 fuck
2025-02-05 pls work
2025-02-06 added vscode back to gitignore
2025-02-06 on the verge of crashing out
2025-02-07 make switch statement
2025-02-07 add script and workflow to compile all tests
2025-02-07 test prod as well
2025-02-07 make sure sharepoint is init'd properly
2025-02-07 remove compile commands
2025-02-07 using sharepoint script now
2025-02-08 rough structure
2025-02-08 wompwomp
2025-02-08 Starter code that hopefully works
2025-02-08 loopback
2025-02-08 fixed event groups (in event_group_test.c)
2025-02-08 pre-main merge
2025-02-08 pre task structure merge
2025-02-08 transitioning to windowed watchdog (WWDG)
2025-02-08 multiple timers :(
2025-02-09 fixed test script
2025-02-09 fixed test script (#8)
2025-02-09 tested with docker script
2025-02-11 started CarCAN init
2025-02-14 PWM_INFO_SIZE
2025-02-15 addressed PR comments: init function for event group, return type for WDog Refresh, Wdog priority
2025-02-15 voltage and temp monitoring tasks update Watchdog task (timer still in the works)
2025-02-15 WINDOW TIMER WORKS !!!!!!!!!!!!!!!!!!!!!!!! super ultra freedom
2025-02-15 oops I deleted something (not important)
2025-02-15 end task scheduler stuff in error handler
2025-02-16 pr stuff
2025-02-16 removed pin debug output; removed gpio parameter from watchdog init
2025-02-18 continue work
2025-02-18 i give up
2025-02-18 Dev update again (#6)
    * started this shit again
    * fuck
    * add .vscode dir
    * pls work
    * fml
    * added vscode back to gitignore
2025-02-19 IWDG update: separated IWDG init and start, removed debug macros, changed name back to IWDG
2025-02-22 changed IWDG task init, deleted GPIO debug, IWDG renaming
2025-02-22 test_IWDG_task builds again
2025-03-01 period elapsed callback
2025-03-02 remove GPIO thing
2025-03-02 IWDG (#4)
    * first IDWG draft
    * modified makefile to allow passed-in stm targets
    * end of day 11/2 commit
    * restructure
    * fixed flash for my makefile
    * fixed ghot spaces in default project target
2025-03-04 still testing
2025-03-08 wahoooooooo!
2025-03-09 added comments and fixed clock enable
2025-03-09 whoops
2025-03-29 preliminary commit - added can_filter file
2025-03-29 can filter works outside of Emb. Sharepoint, need to interface with can1_recv somehow?
2025-04-05 Added functionality for both Mask and List mode; both seem to work
2025-04-05 added documentation and more test cases
2025-04-05 passing in NULL to CAN_Filter_List_Init accepts all IDs
2025-09-13 blah
2025-09-13 test
2025-09-13 Restructure SW/HW (#11)
    * restructure
    * blah
    * test
    * empty
2025-09-24 inital
2025-09-27 BPS-Leader Schematic completed (mostly)
2025-09-28 removed useless txt file
2025-09-29 Completely remove KiCAD-Sharepoint
2025-09-29 added fuse, made kiCad Sharepoint a submodule, added a pulldown, added test-points
2025-09-29 removed redundant .ioc
2025-10-07 Very, very intial layout designed. Many issues. Too bad!
2025-10-07 small fixes
2025-10-07 moved the 24V test point out from under the LSOM
2025-10-10 Redid layout, still missed STEP Files
2025-10-10 removed test-points from under LSOM
2025-10-11 Backup
2025-10-11 all 3d models added, minor fixes
2025-10-13 Rerouted traces to distribute damage to ground plane, labled connectors, added a Charger Can port contected to CarCan Terminals, removed via constriction on main power traces (24V and 3.3V) and expan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
2025-10-13 increased size of post-diode LV zone
2025-10-14 Board GERBER genereated and BOM :)
2025-10-25 Updated Bom 2
2025-10-25 moved files
2025-10-30 Rev A (#12)
    * hi
    * inital
    * BPS-Leader Schematic completed (mostly)
    * Confirmed ESP pin UART Boot-capability, labeled LED's, Moved Power sheet to a nicer location
    * removed useless txt file
    * Completely remove KiCAD-Sharepoint
2025-11-04 wrote contactor driver
2025-11-04 MAYBE
2025-12-21 RevB Schematic Update
2025-12-27 RevB Schematic revisions
2026-01-04 Schematic polishes, layout WIP
2026-01-08 circuit blocks designed, schematic updated
2026-01-08 unblocked SD card holder
2026-01-09 halfway laid-out
2026-01-09 small schematic changes
2026-01-11 intial layout design
2026-01-11 Updated LSOM footprint
2026-01-14 RevB layout completed
2026-01-14 JLC Production Files
2026-01-14 added resistors
2026-01-14 replace silkscreen
2026-01-17 removed all unnessasary files and some nessasary ones
2026-01-18 RevB PR (#14)
    * RevB Schematic Update
    * RevB Schematic revisions
    * revB updates
    * Schematic polishes, layout WIP
    * circuit blocks designed, schematic updated
    * unblocked SD card holder
2026-01-21 put the thing in the thing (folder reorganization)
2026-01-24 TmpHmd
2026-01-26 Added more drivers
2026-01-31 fixed code from comments, makefile fixes
2026-02-02 review changes made
2026-02-07 pinout FIXED for RevB
2026-02-07 Fixed everything
2026-02-24 added new tests
2026-03-02 driver overhaul
2026-03-02 fixed compile errors
2026-03-06 nix fix test
2026-03-06 nix-workflow-fix2
2026-03-06 nix-fix-4
2026-03-06 nix-fix-5
2026-03-08 CAN can communication
2026-03-08 nix stick sucksgit status!
2026-03-10 SHT45 works
2026-03-10 fan driver intializes successfully
2026-03-12 ADC driver from VCU verified
2026-03-14 Precharge is working
2026-03-15 Ravi changes made
2026-03-21 Most review changes made
2026-03-28 ALL changes made (mostly)
2026-03-28 fixed tests
2026-03-28 fixed toggleHeartbeat
2026-03-28 mystery tweaks
2026-03-28 building
2026-03-28 For every review I flipped a coin and fixed it only if it came up heads
2026-03-28 added precharge idle task
2026-03-28 Drivers (#15)
    * initial commit
    * added embedded sharepoint submodule
    * TmpHmd
    * Added more drivers
    * fixed code from comments, makefile fixes
    * review changes made
2026-04-03 amepres task draft
2026-04-03 voltage task works (still refining)
2026-04-04 added temp monitor
2026-04-04 removed fake test
2026-04-04 amperes task running with fault handler, no watchdog yet
2026-04-04 removed HB toggle, reverted some files
2026-04-04 can recv entries
2026-04-05 amperes monitor task
2026-04-05 add can forward to initTask and implement voltage aggregate packing
2026-04-05 fix minor bugs in voltage packing
2026-04-08 addressed comments (except fan task)
2026-04-08 addressed gemini comments
2026-04-08 fixed gemini comments again (commit farming)
2026-04-08 gamebreaking bug fixed
2026-04-10 reviews adressed
2026-04-10 Fixed test issues
2026-04-10 added ESTOP pins software pulldown
2026-04-10 all da faults
2026-04-10 fault leds
2026-04-10 erm safety.....verified ?!
2026-04-10 fix temp packing
2026-04-11 saving before new craig branch
2026-04-11 status message worky
2026-04-11 check for craig
2026-04-11 no fault carcan
2026-04-12 CAN forwarding works again
2026-04-13 Revert "CAN forwarding works again"
    This reverts commit 7bf23614e0438775fc81ef8ec0e0bf2dce1528dc.
2026-04-13 redid can stuff and fixed can forwarding
2026-04-14 precharging refactored & other suprises
2026-04-15 addressed all reviews, fault bits array implmentation and can status refactoring
2026-04-16 state machine improved, mod fault LEDs and STROBE implemented [NOT HARDWARE VERIFIED]
2026-04-18 fixed BPS fault can status message & amperes watchdog
2026-04-18 test pls?
2026-04-18 charging task updates
2026-04-20 added comments + validated with hw
2026-04-25 added ESTOP sense pulldowns
2026-04-25 removed voltage divider
2026-04-27 JLCPCB ouput files
2026-05-23 fixed compilation errors
2026-06-06 put can read and watchdog back
2026-06-12 added heartbeat & changed fan task to closed cycle
2026-06-13 BPSL Task Logic (#16)
    * Volt moniter task
    * voltage task works (still refining)
    * added temp monitor
    * temp monitoring test
    * removed fake test
    * amperes monitor task
2026-06-15 add temp fault histogram
2026-06-15 add static assert to prevent overflowing otemp fault counter
2026-06-19 update again
2026-06-19 started array precharge code
2026-06-20 add tpee datasheet
2026-06-20 not compiling precharge code
2026-06-20 add some precharge debug statements
2026-06-20 forgot to actually enable MPPT in driver
2026-06-20 addressed some reviews
2026-06-20 change fuckah names of variables
2026-06-27 add some extra debug statements in precharge and voltage monitor task
2026-06-27 add printouts to print module faulted values and current values in a fault
2026-06-27 bps workie and more compact printouts
2026-06-27 forgot to reenable vt temp can watchdog
2026-06-28 fix some goofy formatting
2026-06-28 add some extra logic to print out which Contactor faulted
2026-06-28 make output dir relative to script location instead of where it is located
2026-06-28 gemini comments
2026-06-29 address some comments
2026-06-29 overrides
